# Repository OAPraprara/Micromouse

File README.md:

# Micromouse
Micromouse for Ashesi University's First edition of the micromouse competition

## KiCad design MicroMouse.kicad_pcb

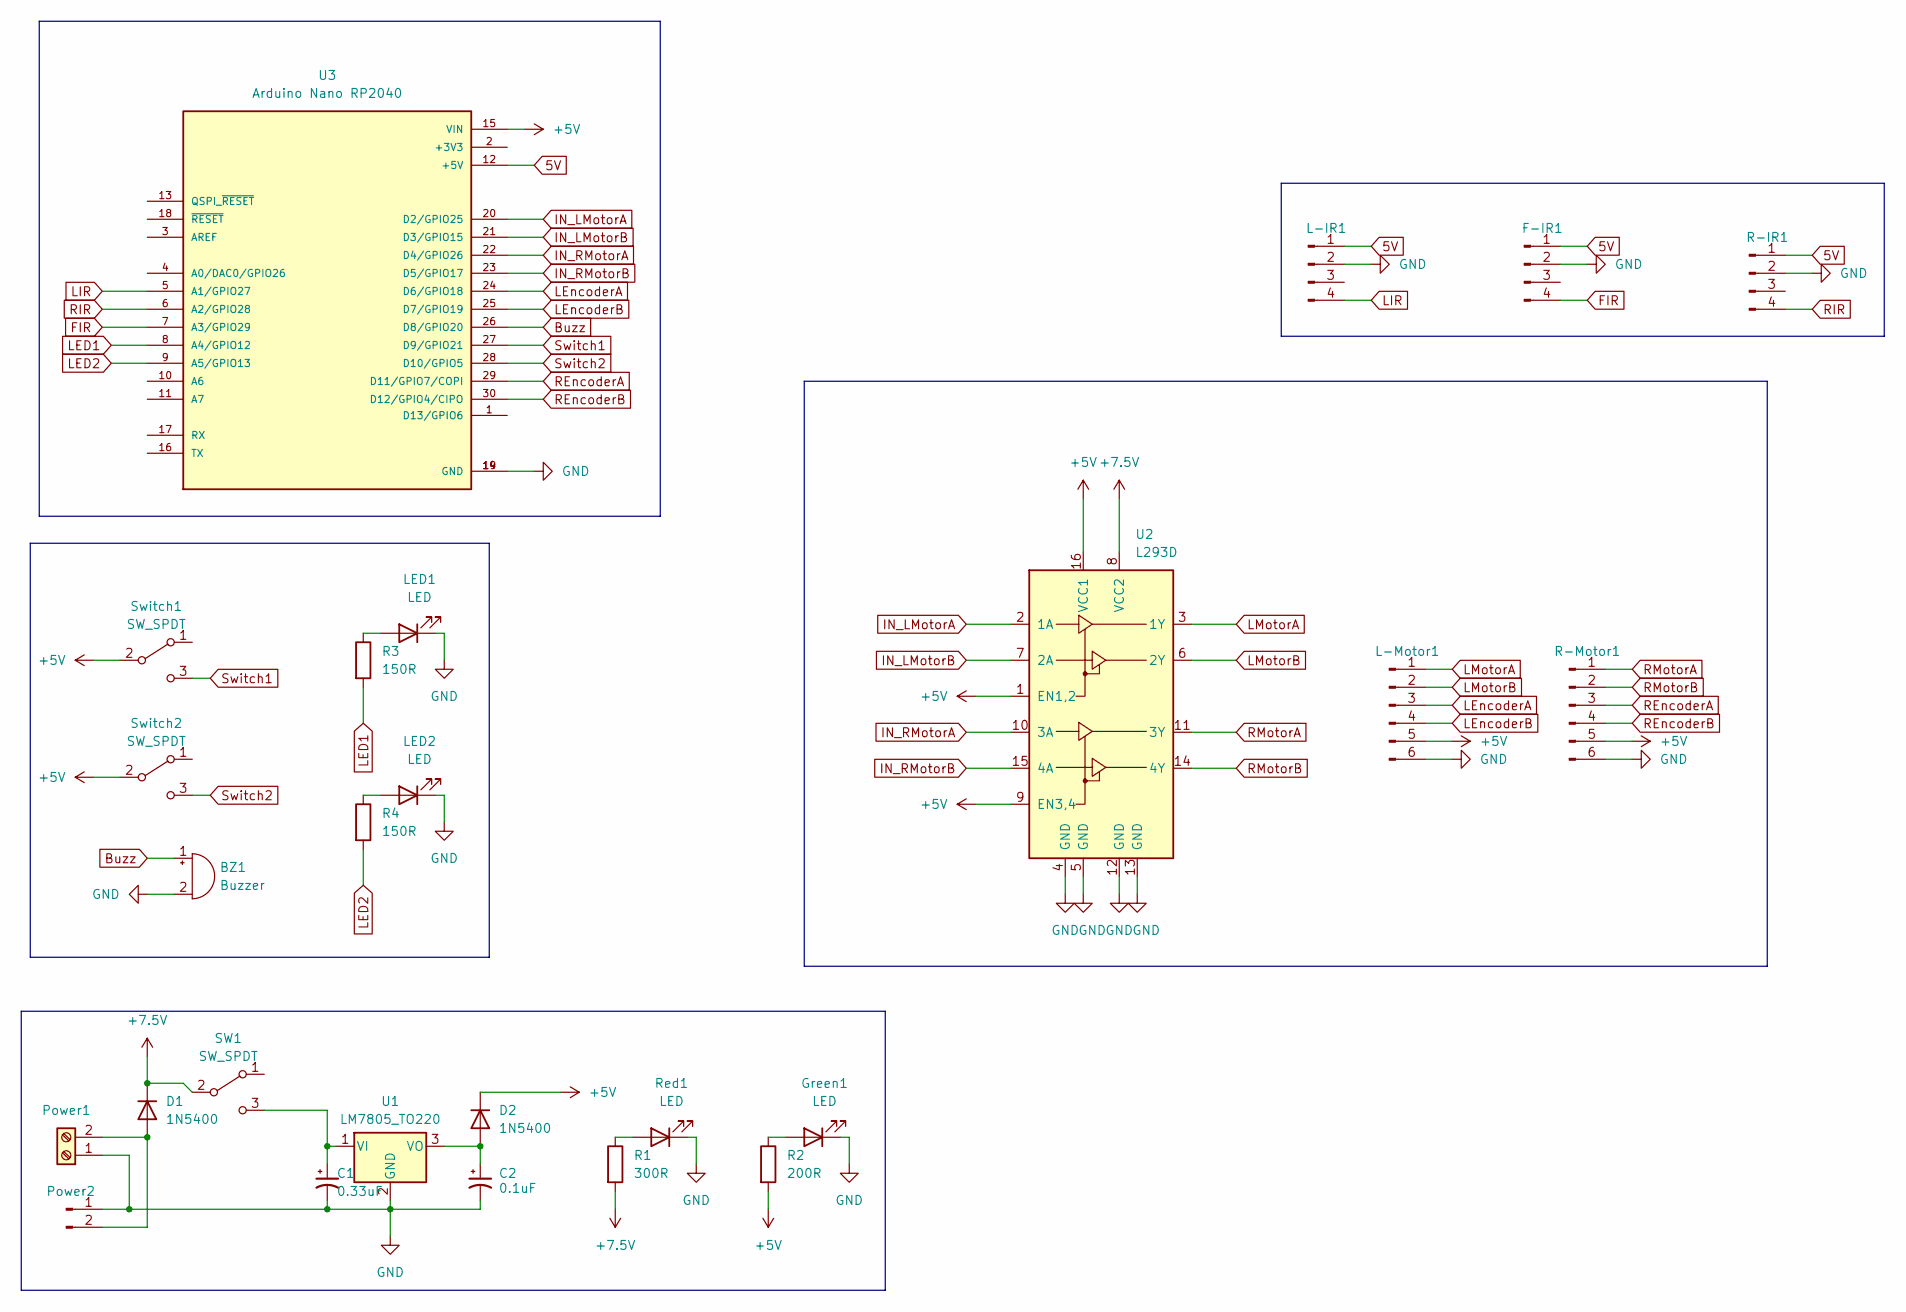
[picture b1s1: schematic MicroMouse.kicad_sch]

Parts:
BZ1: Buzzer; Buzzer_12x9.5RM7.6
C1: 0.33uF; CP_Radial_D4.0mm_P1.50mm
C2: 0.1uF; CP_Radial_D4.0mm_P1.50mm
D1, D2: 1N5400; D_DO-201AD_P5.08mm_Vertical_KathodeUp
F-IR1: Conn_01x04_Pin; PinHeader_1x04_P2.54mm_Vertical
Green1: LED; LED_D5.0mm
L-IR1: Conn_01x04_Pin; PinHeader_1x04_P2.54mm_Vertical
L-Motor1: Conn_01x06_Pin; PinHeader_1x06_P2.54mm_Vertical
LED1, LED2: LED; LED_D5.0mm
Power1: Screw_Terminal_01x02; TerminalBlock_Altech_AK300-2_P5.00mm
Power2: Conn_01x02_Pin; PinHeader_1x02_P2.54mm_Vertical
R1: 300R; R_Axial_DIN0204_L3.6mm_D1.6mm_P1.90mm_Vertical
R2: 200R; R_Axial_DIN0204_L3.6mm_D1.6mm_P1.90mm_Vertical
R3, R4: 150R; R_Axial_DIN0204_L3.6mm_D1.6mm_P1.90mm_Vertical
R-IR1: Conn_01x04_Pin; PinHeader_1x04_P2.54mm_Vertical
R-Motor1: Conn_01x06_Pin; PinHeader_1x06_P2.54mm_Vertical
Red1: LED; LED_D5.0mm
SW1: SW_SPDT; SW_1825159-1
Switch1, Switch2: SW_SPDT; SW_1825159-1
U1: LM7805_TO220; TO-220-3_Vertical
U2: L293D; DIP-16_W7.62mm
U3: Arduino Nano RP2040; MODULE_ABX00053; PARTREV Rev. 01 - 14/05/2021

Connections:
5V: F-IR1.1, L-IR1.1, R-IR1.1, U3.12 (+5V)
+5V: D2.1 (K), L-Motor1.5, R2.2, R-Motor1.5, Switch1.2 (B), Switch2.2 (B), U2.1 (EN1,2), U2.9 (EN3,4), U2.16 (VCC1), U3.15 (VIN)
+7.5V: D1.1 (K), R1.2, SW1.2 (B), U2.8 (VCC2)
Buzz: BZ1.1 (-), U3.26 (D8/GPIO20)
FIR: F-IR1.4, U3.7 (A3/GPIO29)
GND: BZ1.2 (+), C1.2, C2.2, F-IR1.2, Green1.1 (K), L-IR1.2, L-Motor1.6, LED1.1 (K), LED2.1 (K), Power1.1, Power2.1, R-IR1.2, R-Motor1.6, Red1.1 (K), U1.2 (GND), U2.4 (GND), U2.5 (GND), U2.12 (GND), U2.13 (GND), U3.14 (GND), U3.19 (GND)
IN_LMotorA: U2.2 (1A), U3.20 (D2/GPIO25)
IN_LMotorB: U2.7 (2A), U3.21 (D3/GPIO15)
IN_RMotorA: U2.10 (3A), U3.22 (D4/GPIO26)
IN_RMotorB: U2.15 (4A), U3.23 (D5/GPIO17)
LED1: R3.2, U3.8 (A4/GPIO12)
LED2: R4.2, U3.9 (A5/GPIO13)
LEncoderA: L-Motor1.3, U3.24 (D6/GPIO18)
LEncoderB: L-Motor1.4, U3.25 (D7/GPIO19)
LIR: L-IR1.4, U3.5 (A1/GPIO27)
LMotorA: L-Motor1.1, U2.3 (1Y)
LMotorB: L-Motor1.2, U2.6 (2Y)
unnamed: D1.2 (A), Power1.2, Power2.2
unnamed: C2.1, D2.2 (A), U1.3 (VO)
unnamed: Green1.2 (A), R2.1
unnamed: LED1.2 (A), R3.1
unnamed: LED2.2 (A), R4.1
unnamed: R1.1, Red1.2 (A)
unnamed: C1.1, SW1.3 (C), U1.1 (VI)
REncoderA: R-Motor1.3, U3.29 (D11/GPIO7/COPI)
REncoderB: R-Motor1.4, U3.30 (D12/GPIO4/CIPO)
RIR: R-IR1.4, U3.6 (A2/GPIO28)
RMotorA: R-Motor1.1, U2.11 (3Y)
RMotorB: R-Motor1.2, U2.14 (4Y)
Switch1: Switch1.3 (C), U3.27 (D9/GPIO21)
Switch2: Switch2.3 (C), U3.28 (D10/GPIO5)

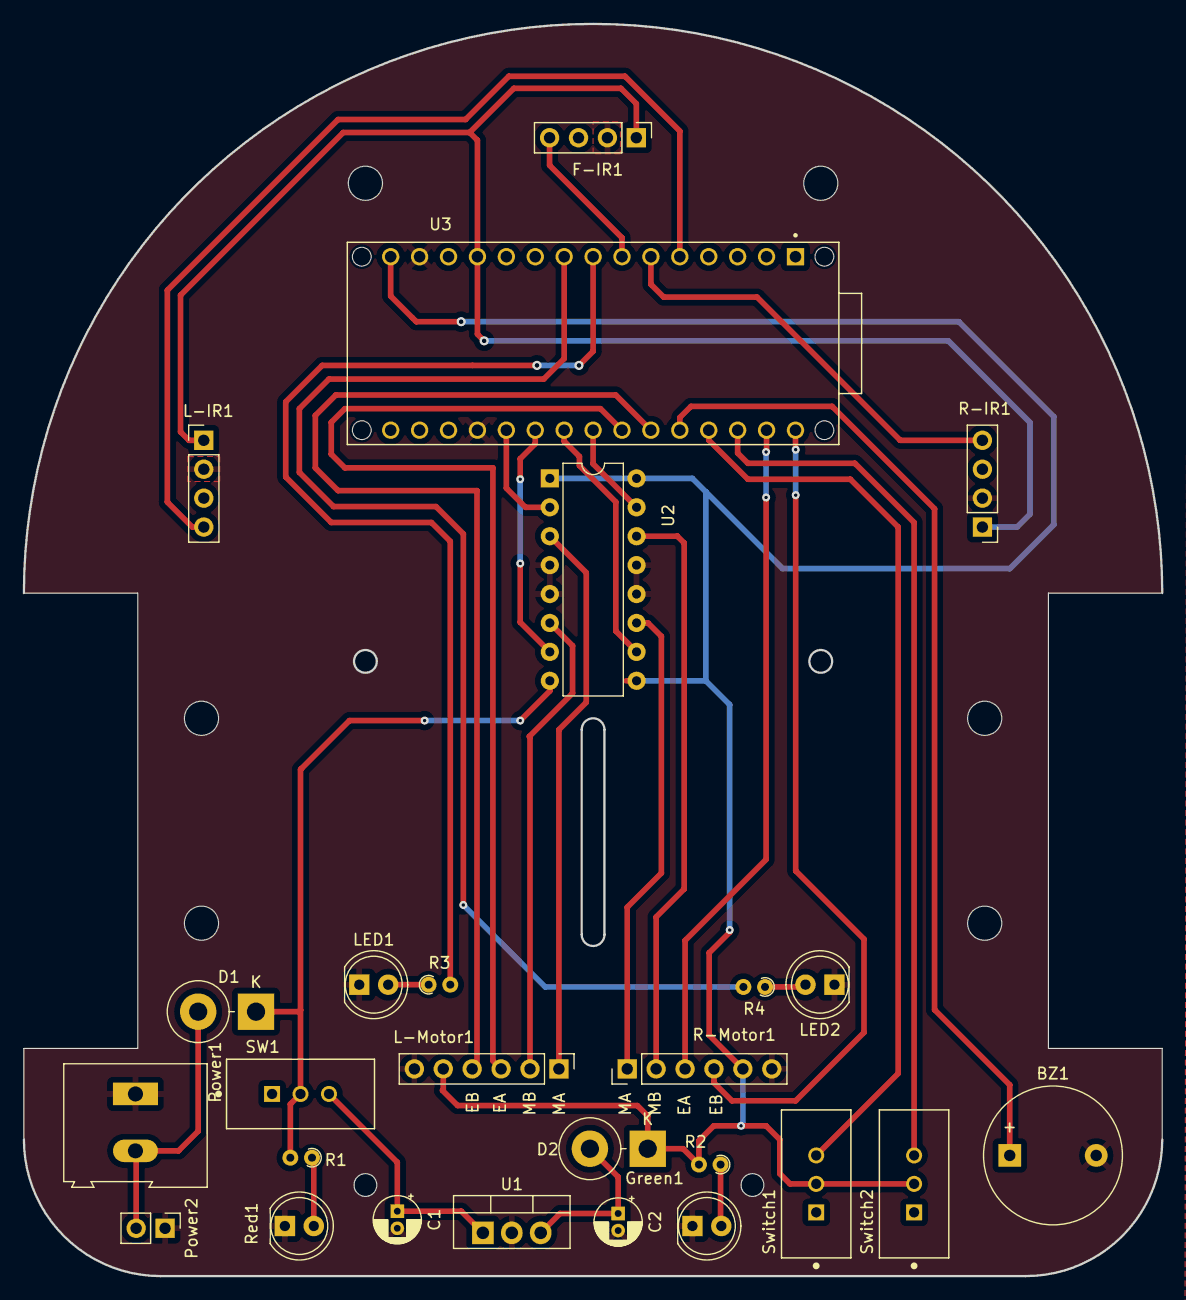
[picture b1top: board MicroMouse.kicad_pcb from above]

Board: 2 copper layers, 100.0 x 110.0 mm, 26 parts (0 on the bottom side), 31 nets.

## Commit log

2025-06-30 Rename PCB 2D vied.jpg to PCB 2D view.jpg
